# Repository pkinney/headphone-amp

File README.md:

Headphone Amp Circuit Design
===

Based on the CMOY designs: https://tangentsoft.net/audio/cmoy/

These files may be an older version of Eagle as they have not been updated in several years.

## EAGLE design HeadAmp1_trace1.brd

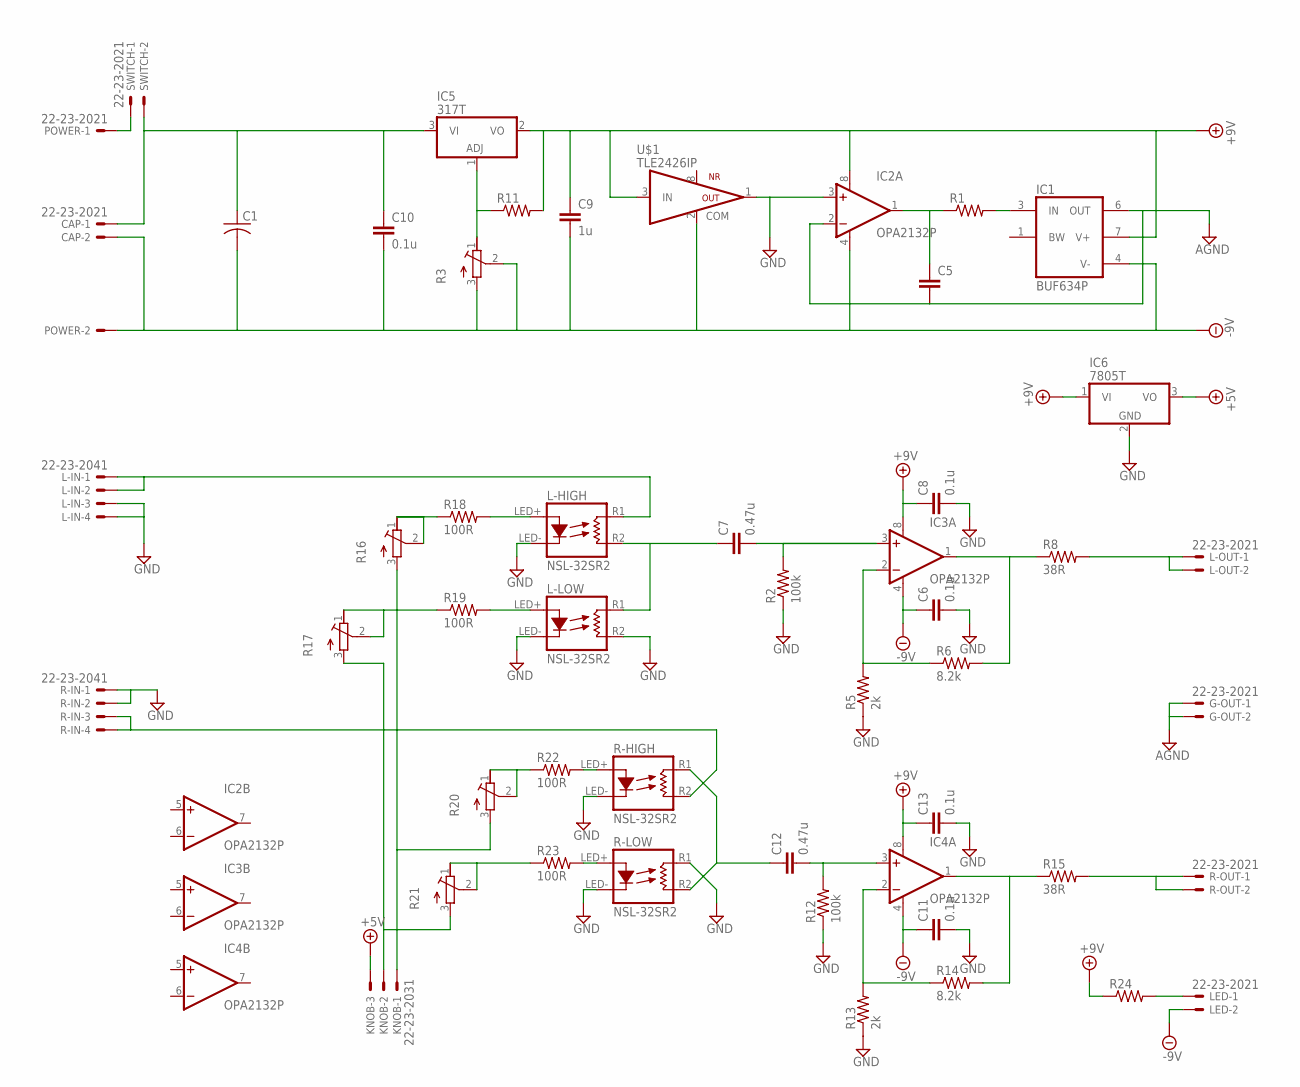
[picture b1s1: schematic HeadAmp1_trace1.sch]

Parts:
C1: C-US050-075X075; C050-075X075
C5: C5/3; C5B3
C6, C8, C10, C11, C13: 0.1u; C5B3
C7, C12: 0.47u; C5B3
C9: 1u; C5B3
CAP: 22-23-2021
G-OUT: 22-23-2021
IC1: BUF634P; DIL08
IC2, IC3, IC4: OPA2132P; DIL08
IC5: 317T; TO220H
IC6: 7805T; TO220H
KNOB: 22-23-2031
L-HIGH: NSL-32SR2; OPTO_32SR
L-IN: 22-23-2041
L-LOW: NSL-32SR2; OPTO_32SR
L-OUT: 22-23-2021
LED: 22-23-2021
POWER: 22-23-2021
R1, R11, R24: R-US_0207/10; 0207/10
R2, R12: 100k; 0207/10
R3, R16, R17, R20, R21: R-TRIMMT93YB; RTRIMT93YB
R5, R13: 2k; 0207/10
R6, R14: 8.2k; 0207/10
R8, R15: 38R; 0207/10
R18, R19, R22, R23: 100R; 0207/10
R-HIGH: NSL-32SR2; OPTO_32SR
R-IN: 22-23-2041
R-LOW: NSL-32SR2; OPTO_32SR
R-OUT: 22-23-2021
SWITCH: 22-23-2021
U$1: TLE2426IP; DIL08

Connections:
+5V: IC6.3 (VO), KNOB.3
+9V: C8.1, C9.1, C13.1, IC1.7 (V+), IC2.8 (V+), IC3.8 (V+), IC4.8 (V+), IC5.2 (VO), IC6.1 (VI), R11.2, R24.1, U$1.3 (IN)
-9V: C1.2, C6.1, C9.2, C10.2, C11.1, CAP.2, IC1.4 (V-), IC2.4 (V-), IC3.4 (V-), IC4.4 (V-), LED.2, POWER.2, R3.2 (S), R3.3 (E), U$1.2 (COMMON)
AGND: C5.2, G-OUT.1, G-OUT.2, IC1.6 (OUT), IC2.2 (-IN)
GND: C6.2, C8.2, C11.2, C13.2, IC2.3 (+IN), IC6.2 (GND), L-HIGH.LED- (C), L-IN.3, L-IN.4, L-LOW.LED- (C), L-LOW.R2 (L2), R2.1, R5.1, R12.1, R13.1, R-HIGH.LED- (C), R-IN.1, R-IN.2, R-LOW.LED- (C), R-LOW.R1 (L1), U$1.1 (OUT)
unnamed: IC3.2 (-IN), R5.2, R6.1
unnamed: IC3.1 (OUT), R6.2, R8.1
unnamed: C7.2, IC3.3 (+IN), R2.2
unnamed: IC5.1 (ADJ), R3.1 (A), R11.1
unnamed: C5.1, IC2.1 (OUT), R1.1
unnamed: IC1.3 (IN), R1.2
unnamed: IC4.2 (-IN), R13.2, R14.1
unnamed: L-OUT.1, L-OUT.2, R8.2
unnamed: IC4.1 (OUT), R14.2, R15.1
unnamed: C12.2, IC4.3 (+IN), R12.2
unnamed: C1.1, C10.1, CAP.1, IC5.3 (VI), SWITCH.2
unnamed: R15.2, R-OUT.1, R-OUT.2
unnamed: L-HIGH.R1 (L1), L-IN.1, L-IN.2
unnamed: C7.1, L-HIGH.R2 (L2), L-LOW.R1 (L1)
unnamed: R16.1 (A), R16.2 (S), R18.1
unnamed: R17.1 (A), R17.2 (S), R19.1
unnamed: KNOB.1, R16.3 (E), R20.3 (E)
unnamed: KNOB.2, R17.3 (E), R21.3 (E)
unnamed: L-HIGH.LED+ (A), R18.2
unnamed: L-LOW.LED+ (A), R19.2
unnamed: R-HIGH.R2 (L2), R-IN.3, R-IN.4
unnamed: C12.1, R-HIGH.R1 (L1), R-LOW.R2 (L2)
unnamed: R20.1 (A), R20.2 (S), R22.1
unnamed: R21.1 (A), R21.2 (S), R23.1
unnamed: POWER.1, SWITCH.1
unnamed: LED.1, R24.2
unnamed: R22.2, R-HIGH.LED+ (A)
unnamed: R23.2, R-LOW.LED+ (A)

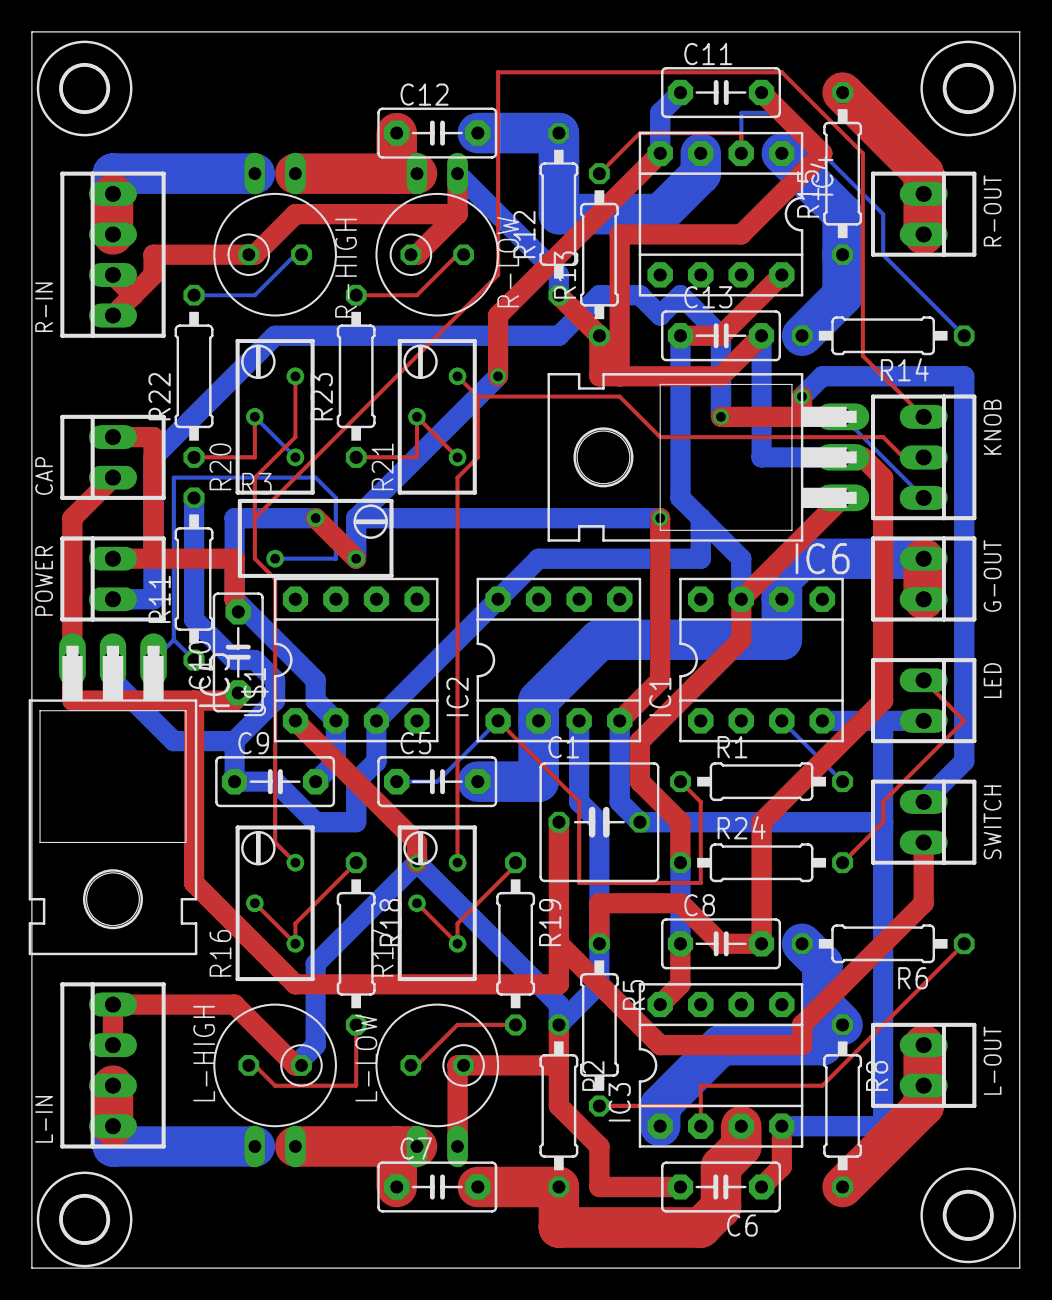
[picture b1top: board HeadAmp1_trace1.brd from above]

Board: 2 copper layers, 61.9 x 77.5 mm, 55 parts (0 on the bottom side), 33 nets.

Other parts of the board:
U$2, U$3, U$4, U$5: 2,8

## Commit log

2020-09-25 Adding exported images
